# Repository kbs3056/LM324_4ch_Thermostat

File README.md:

# LM324_4ch_Thermostat
Four input thermostat with one OC output.

PCB approx 21x21mm.

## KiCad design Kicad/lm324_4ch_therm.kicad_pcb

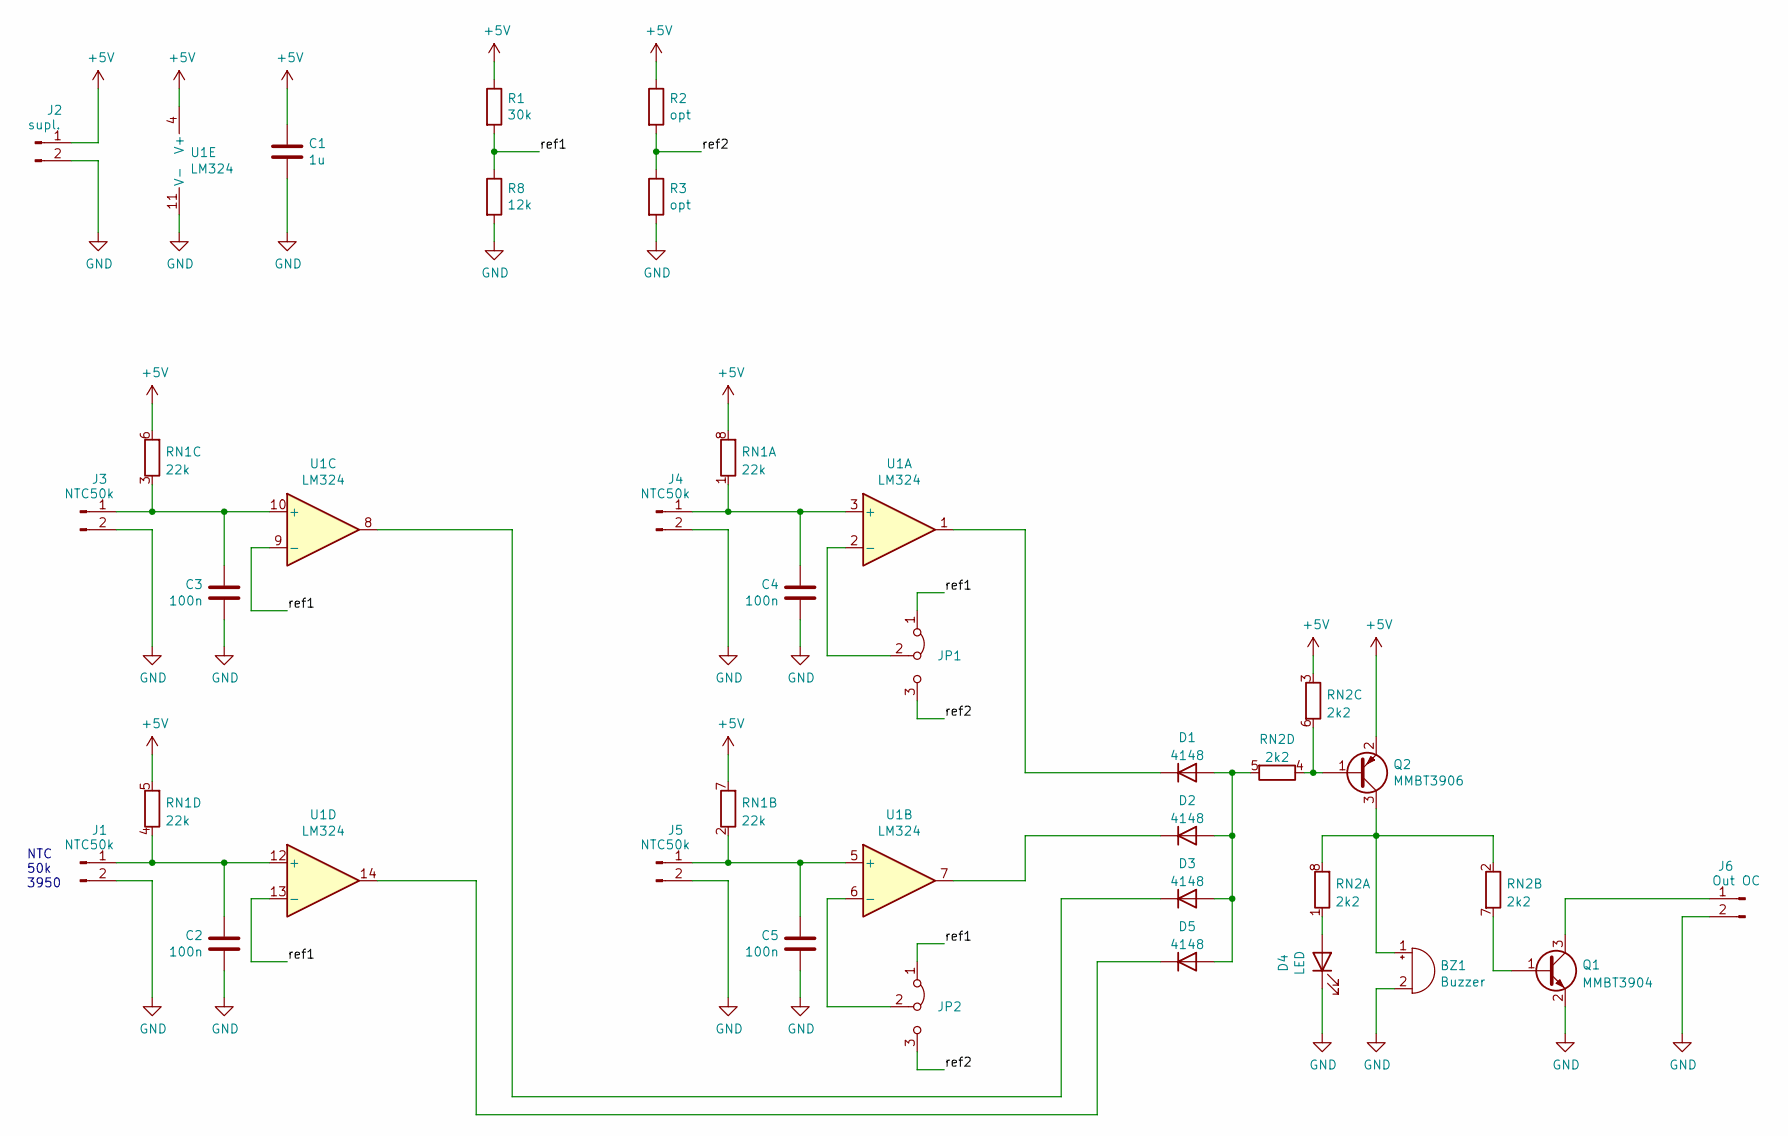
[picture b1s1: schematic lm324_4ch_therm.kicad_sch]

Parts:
BZ1: Buzzer; MagneticBuzzer_Kingstate_KCG0601
C1: 1u; C_0805_2012Metric
C2, C3, C4, C5: 100n; C_0805_2012Metric
D1, D2, D3, D5: 4148; D_MiniMELF
D4: LED; LED_D3.0mm
J1, J3, J4, J5: NTC50k; PinSocket_1x02_P2.54mm_Vertical
J2: supl.; PinSocket_1x02_P2.54mm_Vertical
J6: Out OC; PinSocket_1x02_P2.54mm_Vertical
JP1, JP2: Jumper_3_Bridged12; SolderJumper-3_P1.3mm_Bridged12_RoundedPad1.0x1.5mm_NumberL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
Q1: MMBT3904; SOT-23
Q2: MMBT3906; SOT-23
R1: 30k; R_1206_3216Metric
R2, R3: opt; R_1206_3216Metric
R8: 12k; R_1206_3216Metric
RN1: 22k; R_Array_Convex_4x0603
RN2: 2k2; R_Array_Convex_4x0603
U1: LM324; SOIC-14_3.9x8.7mm_P1.27mm

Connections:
+5V: C1.1, J2.1, Q2.2 (E), R1.1, R2.1, RN1.5 (R4.2), RN1.6 (R3.2), RN1.7 (R2.2), RN1.8 (R1.2), RN2.3 (R3.1), U1.4 (V+)
/ref1: JP1.1 (A), JP2.1 (A), R1.2, R8.1, U1.9 (-), U1.13 (-)
/ref2: JP1.3 (B), JP2.3 (B), R2.2, R3.1
GND: BZ1.2 (+), C1.2, C2.1, C3.1, C4.1, C5.1, D4.1 (K), J1.2, J2.2, J3.2, J4.2, J5.2, J6.2, Q1.2 (E), R3.2, R8.2, U1.11 (V-)
unnamed: D1.2 (A), D2.2 (A), D3.2 (A), D5.2 (A), RN2.5 (R4.2)
unnamed: D4.2 (A), RN2.1 (R1.1)
unnamed: C2.2, J1.1, RN1.4 (R4.1), U1.12 (+)
unnamed: J6.1, Q1.3 (C)
unnamed: Q1.1 (B), RN2.7 (R2.2)
unnamed: Q2.1 (B), RN2.4 (R4.1), RN2.6 (R3.2)
unnamed: BZ1.1 (-), Q2.3 (C), RN2.2 (R2.1), RN2.8 (R1.2)
unnamed: D1.1 (K), U1.1
unnamed: JP1.2 (C), U1.2 (-)
unnamed: C4.2, J4.1, RN1.1 (R1.1), U1.3 (+)
unnamed: C5.2, J5.1, RN1.2 (R2.1), U1.5 (+)
unnamed: JP2.2 (C), U1.6 (-)
unnamed: D2.1 (K), U1.7
unnamed: D3.1 (K), U1.8
unnamed: C3.2, J3.1, RN1.3 (R3.1), U1.10 (+)
unnamed: D5.1 (K), U1.14

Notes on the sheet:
NTC 50k 3950

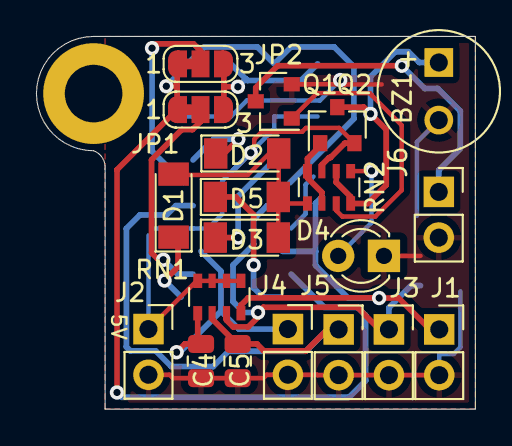
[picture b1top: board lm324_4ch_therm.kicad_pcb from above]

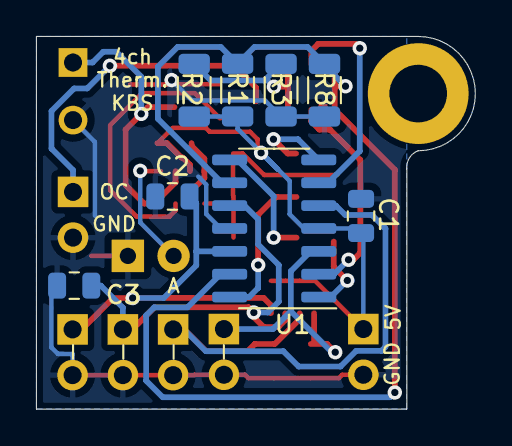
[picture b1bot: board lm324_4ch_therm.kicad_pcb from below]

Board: 2 copper layers, 24.4 x 20.7 mm, 29 parts (8 on the bottom side), 20 nets.

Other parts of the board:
REF2: MountingHole_3.2mm_M3_DIN965_Pad

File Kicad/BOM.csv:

Id,Designator,Package,Quantity,Designation,Description
1,"J1,J5,J4,J3",PinSocket_1x02_P2.54mm_Vertical,4,NTC50k,
2,D4,LED_D3.0mm,1,LED,
3,J2,PinSocket_1x02_P2.54mm_Vertical,1,supl.,
4,BZ1,MagneticBuzzer_Kingstate_KCG0601,1,Buzzer,5V gen.
5,"D1,D3,D5,D2",D_MiniMELF,4,1N4148,
6,RN2,R_Array_Convex_4x0603,1,2k2,
7,RN1,R_Array_Convex_4x0603,1,22k,
8,"JP2,JP1",SolderJumper-3_P1.3mm_Bridged12_RoundedPad1.0x1.5mm_NumberLabels,2,Jumper_3_Bridged12,
9,Q1,SOT-23,1,MMBT3904,
10,"C4,C5,C2,C3",C_0805_2012Metric,4,100n,
11,Q2,SOT-23,1,MMBT3906,
12,J6,PinSocket_1x02_P2.54mm_Vertical,1,Out OC,
13,C1,C_0805_2012Metric,1,1u,
14,R8,R_1206_3216Metric,1,12k,
15,U1,SOIC-14_3.9x8.7mm_P1.27mm,1,LM324,
16,R1,R_1206_3216Metric,1,30k,
17,"R2,R3",R_1206_3216Metric,2,opt,Optional
